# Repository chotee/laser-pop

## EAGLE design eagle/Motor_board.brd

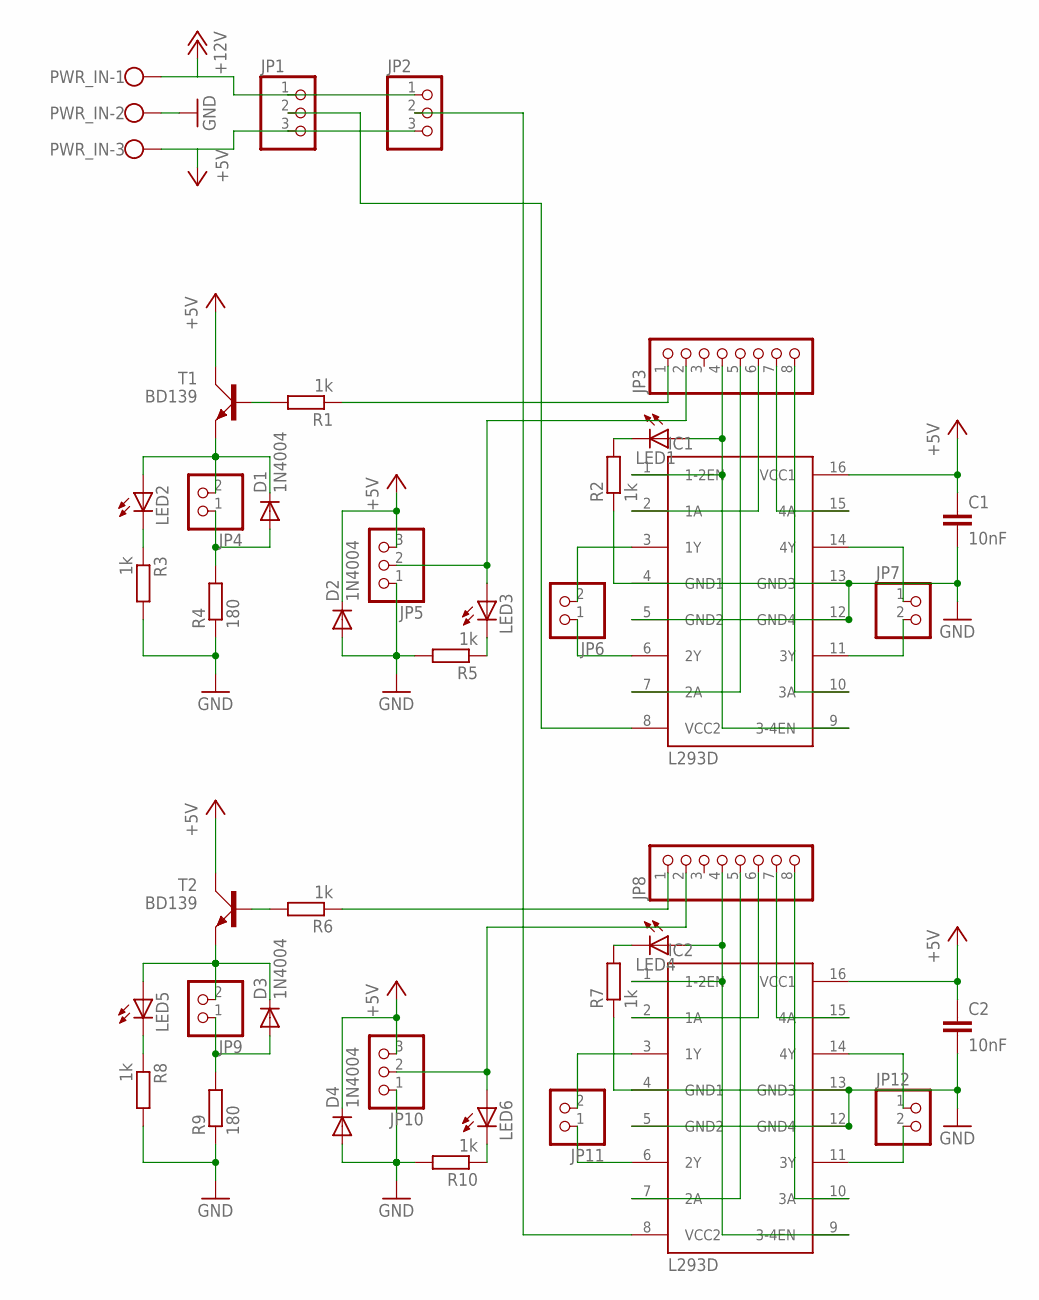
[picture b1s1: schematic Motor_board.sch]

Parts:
C1, C2: 10nF; C050-024X044
D1, D2, D3, D4: 1N4004; DO41-10
IC1, IC2: L293D; DIL16
JP1, JP2, JP5, JP10: PINHD-1X3; 1X03
JP3, JP8: PINHD-1X8; 1X08
JP4, JP6, JP7, JP9, JP11, JP12: PINHD-1X2; 1X02
LED1, LED2, LED3, LED4, LED5, LED6: LED3MM
PWR_IN: W237-103
R1, R2, R3, R5, R6, R7, R8, R10: 1k; 0207/7
R4, R9: 180; 0414V
T1, T2: BD139; TO126AV

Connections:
+5V: C1.1, C2.1, D2.C, D4.C, IC1.16 (VCC1), IC2.16 (VCC1), JP1.3, JP2.3, JP5.3, JP10.3, PWR_IN.3, T1.C, T2.C
+12V: JP1.1, JP2.1, PWR_IN.1
GND: C1.2, C2.2, D2.A, D4.A, IC1.4 (GND1), IC1.5 (GND2), IC1.12 (GND4), IC1.13 (GND3), IC2.4 (GND1), IC2.5 (GND2), IC2.12 (GND4), IC2.13 (GND3), JP5.1, JP10.1, PWR_IN.2, R2.1, R3.2, R4.1, R5.2, R7.1, R8.2, R9.1, R10.2
MTR_PWR1: IC1.8 (VCC2), JP1.2
MTR_PWR2: IC2.8 (VCC2), JP2.2
unnamed: IC2.1 (1-2EN), IC2.9 (3-4EN), JP8.4, LED4.A
unnamed: IC2.2 (1A), JP8.6
unnamed: IC2.7 (2A), JP8.5
unnamed: IC2.3 (1Y), JP11.2
unnamed: IC2.6 (2Y), JP11.1
unnamed: IC2.11 (3Y), JP12.2
unnamed: IC1.1 (1-2EN), IC1.9 (3-4EN), JP3.4, LED1.A
unnamed: IC1.10 (3A), JP3.8
unnamed: IC2.14 (4Y), JP12.1
unnamed: IC1.2 (1A), JP3.6
unnamed: IC1.7 (2A), JP3.5
unnamed: IC1.15 (4A), JP3.7
unnamed: IC2.10 (3A), JP8.8
unnamed: IC1.3 (1Y), JP6.2
unnamed: IC1.6 (2Y), JP6.1
unnamed: IC1.11 (3Y), JP7.2
unnamed: IC1.14 (4Y), JP7.1
unnamed: IC2.15 (4A), JP8.7
unnamed: R6.2, T2.B
unnamed: JP8.1, R6.1
unnamed: JP8.2, JP10.2, LED6.A
unnamed: D3.A, JP9.1, R9.2
unnamed: LED1.K (C), R2.2
unnamed: R1.2, T1.B
unnamed: JP3.1, R1.1
unnamed: D1.A, JP4.1, R4.2
unnamed: JP3.2, JP5.2, LED3.A
unnamed: D3.C, JP9.2, LED5.A, T2.E
unnamed: LED5.K (C), R8.1
unnamed: LED4.K (C), R7.2
unnamed: LED6.K (C), R10.1
unnamed: D1.C, JP4.2, LED2.A, T1.E
unnamed: LED2.K (C), R3.1
unnamed: LED3.K (C), R5.1

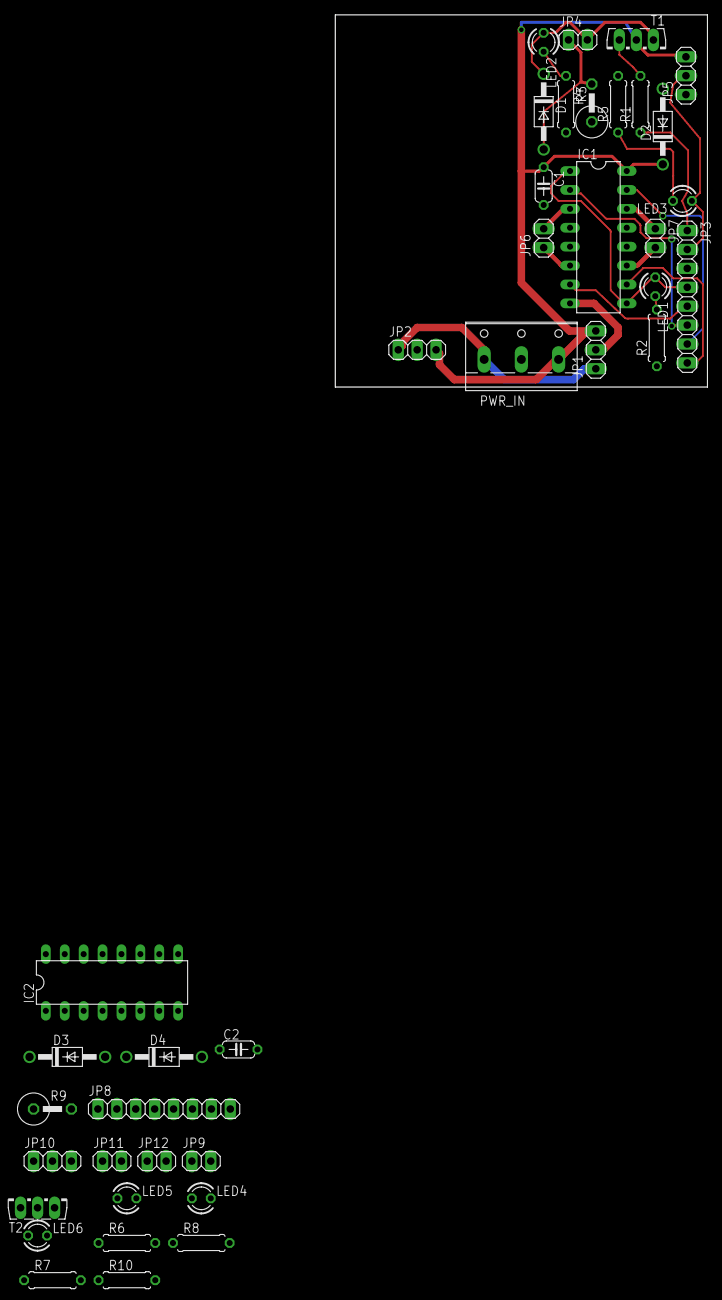
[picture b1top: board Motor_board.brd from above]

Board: 2 copper layers, 50.0 x 50.0 mm, 39 parts (0 on the bottom side), 39 nets.

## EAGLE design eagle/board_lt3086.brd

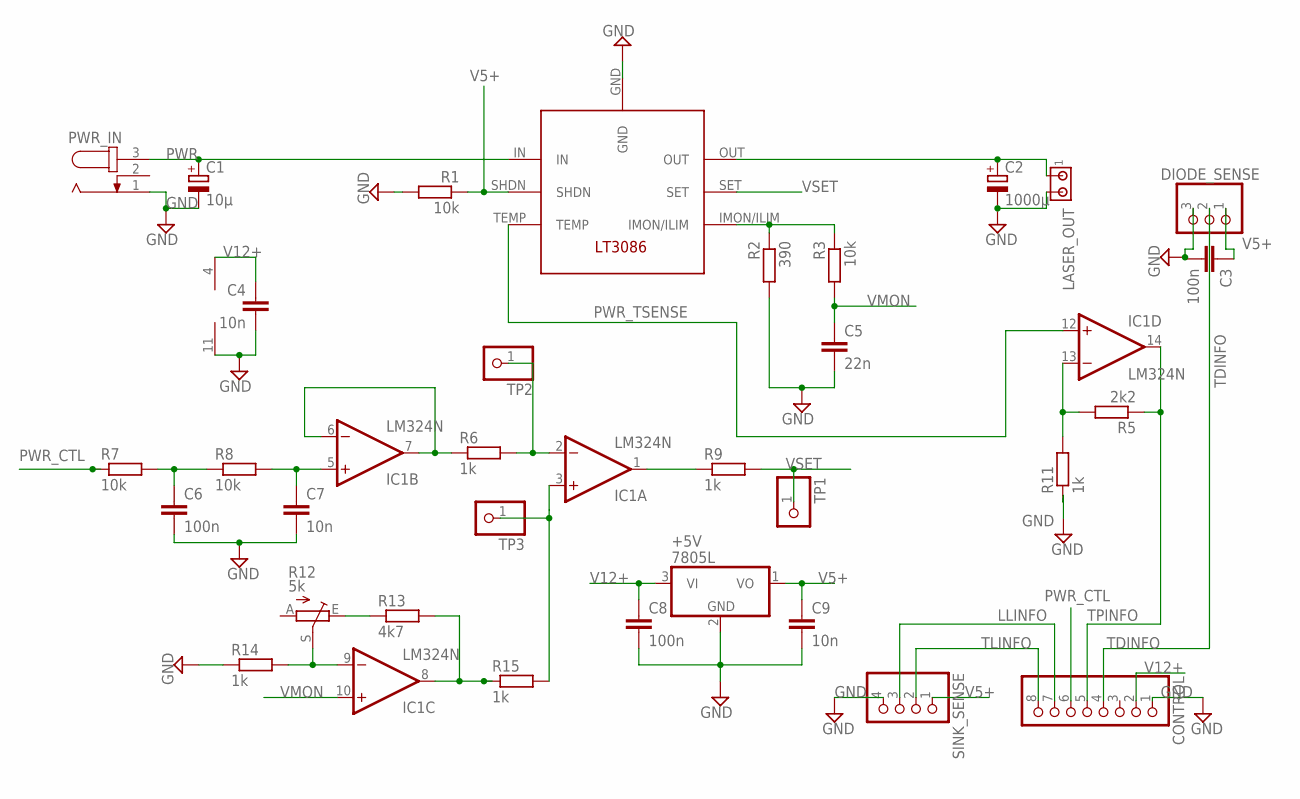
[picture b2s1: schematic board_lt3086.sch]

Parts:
+5V: 7805L; TO92
C1: 10µ; E2,5-7
C2: 1000µ; E3,5-10
C3, C6, C8: 100n; C050-035X075
C4, C7, C9: 10n; C050-024X044
C5: 22n; C050-024X044
CONTROL: PINHD-1X8; 1X08
DIODE_SENSE: PINHD-1X3; 1X03
IC1: LM324N; DIL14
LASER_OUT: 350428-1
PWR_CTRL: LT3086; LT3086-T7
PWR_IN: JACK-PLUG0; SPC4077
R1, R3, R7, R8: 10k; 0207/10
R2: 390; 0207/10
R5: 2k2; 0207/10
R6, R9, R11, R14, R15: 1k; 0207/10
R12: 5k; CA9V
R13: 4k7; 0207/10
SINK_SENSE: PINHD-1X4; 1X04
TP1, TP2, TP3: PINHD-1X1; 1X01

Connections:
GND: +5V.2 (GND), C1.-, C2.-, C3.2, C4.2, C5.2, C6.2, C7.2, C8.2, C9.2, CONTROL.1, DIODE_SENSE.3, IC1.11 (V-), LASER_OUT.2, PWR_CTRL.GND, PWR_IN.1, R1.2, R2.2, R11.1, R14.1, SINK_SENSE.4
LLINFO: CONTROL.7, SINK_SENSE.3
unnamed: IC1.6 (-IN), IC1.7 (OUT), R6.1
unnamed: C7.1, IC1.5 (+IN), R8.2
unnamed: C6.1, R7.2, R8.1
unnamed: IC1.1 (OUT), R9.1
unnamed: IC1.13 (-IN), R5.2, R11.2
unnamed: IC1.2 (-IN), R6.2, TP2.1
unnamed: IC1.3 (+IN), R15.2, TP3.1
unnamed: IC1.8 (OUT), R13.2, R15.1
unnamed: R12.E, R13.1
unnamed: IC1.9 (-IN), R12.S, R14.2
unnamed: PWR_CTRL.IMON/ILIM, R2.1, R3.1
PWR: C1.+, PWR_CTRL.IN, PWR_IN.3
PWR_CTL: CONTROL.6, R7.1
PWR_TSENSE: IC1.12 (+IN), PWR_CTRL.TEMP
TDINFO: CONTROL.4, DIODE_SENSE.2
TLINFO: CONTROL.8, SINK_SENSE.2
TPINFO: CONTROL.5, IC1.14 (OUT), R5.1
V5+: +5V.1 (VO), C3.1, C9.1, DIODE_SENSE.1, PWR_CTRL.SHDN, R1.1, SINK_SENSE.1
V12+: +5V.3 (VI), C4.1, C8.1, CONTROL.2, IC1.4 (V+)
VMON: C5.1, IC1.10 (+IN), R3.2
VOUT: C2.+, LASER_OUT.1, PWR_CTRL.OUT
VSET: PWR_CTRL.SET, R9.2, TP1.1

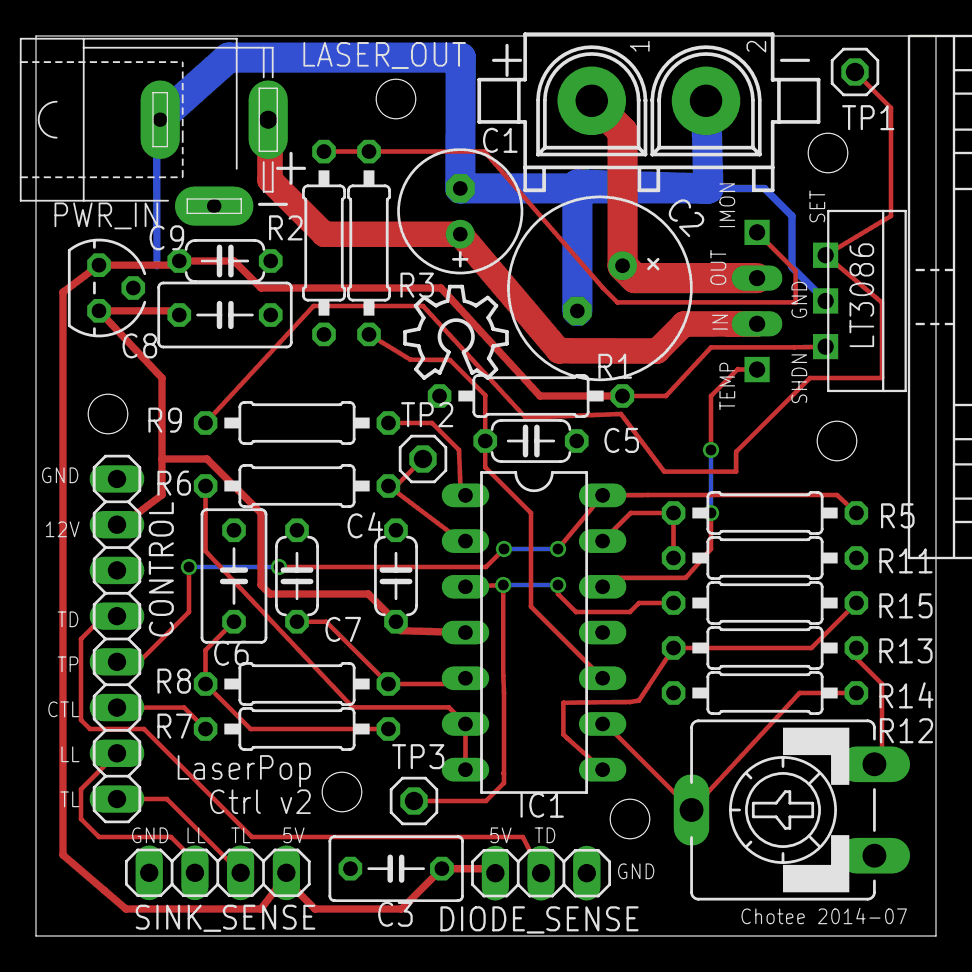
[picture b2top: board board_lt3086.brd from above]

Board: 2 copper layers, 50.0 x 50.0 mm, 35 parts (0 on the bottom side), 24 nets.

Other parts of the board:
U$1: OSHW_8X200_NOTEXT
U$2: HEATSINK-11C/W

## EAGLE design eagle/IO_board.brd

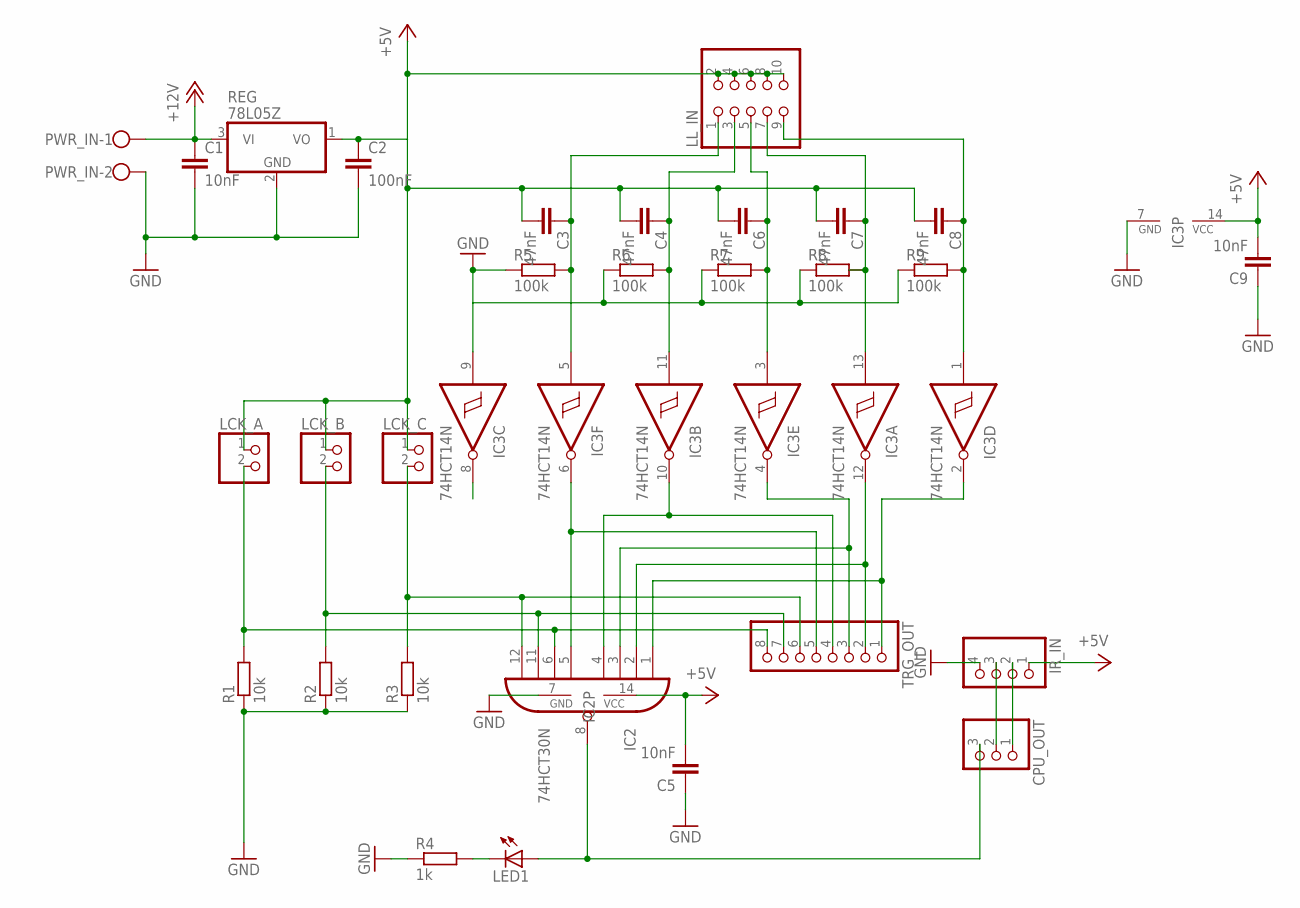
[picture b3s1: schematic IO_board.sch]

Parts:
C1: 10nF; C025-025X050
C2: 100nF; C025-025X050
C3, C4, C6, C7, C8: 47nF; C025-025X050
C5, C9: 10nF; C050-024X044
CPU_OUT: PINHD-1X3; 1X03
IC2: 74HCT30N; DIL14
IC3: 74HCT14N; DIL14
IR_IN: PINHD-1X4; 1X04
LCK_A: PINHD-1X2; 1X02
LCK_B: PINHD-1X2; 1X02
LCK_C: PINHD-1X2; 1X02
LED1: LED3MM
LL_IN: PINHD-2X5; 2X05
PWR_IN: W237-102
R1, R2, R3: 10k; 0207/7
R4: 1k; 0207/7
R5, R6, R7, R8, R9: 100k; 0207/7
REG: 78L05Z; TO92
TRG_OUT: PINHD-1X8; 1X08

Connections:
+5V: C2.1, C3.2, C4.2, C5.2, C6.2, C7.2, C8.2, C9.2, IC2.14 (VCC), IC3.14 (VCC), IR_IN.1, LCK_A.1, LCK_B.1, LCK_C.1, LL_IN.2, LL_IN.4, LL_IN.6, LL_IN.8, LL_IN.10, REG.1 (VO)
+12V: C1.1, PWR_IN.1, REG.3 (VI)
GND: C1.2, C2.2, C5.1, C9.1, IC2.7 (GND), IC3.7 (GND), IR_IN.4, PWR_IN.2, R1.1, R2.1, R3.1, R4.1, R5.1, R6.1, R7.1, R8.1, R9.1, REG.2 (GND)
unnamed: IC2.2 (I1), IC3.12 (O), TRG_OUT.2
unnamed: IC2.4 (I3), IC3.10 (O), TRG_OUT.4
unnamed: IC2.1 (I0), IC3.2 (O), TRG_OUT.1
unnamed: CPU_OUT.3, IC2.8 (O), LED1.A
unnamed: C4.1, IC3.11 (I), LL_IN.3, R6.2
unnamed: CPU_OUT.2, IR_IN.3
unnamed: C6.1, IC3.3 (I), LL_IN.5, R7.2
unnamed: C7.1, IC3.13 (I), LL_IN.7, R8.2
unnamed: C8.1, IC3.1 (I), LL_IN.9, R9.2
unnamed: CPU_OUT.1, IR_IN.2
unnamed: IC2.5 (I4), IC3.6 (O), TRG_OUT.5
unnamed: C3.1, IC3.5 (I), LL_IN.1, R5.2
unnamed: IC2.3 (I2), IC3.4 (O), TRG_OUT.3
unnamed: IC2.12 (I7), LCK_C.2, R3.2, TRG_OUT.6
unnamed: IC2.11 (I6), LCK_B.2, R2.2, TRG_OUT.7
unnamed: IC2.6 (I5), LCK_A.2, R1.2, TRG_OUT.8
unnamed: LED1.K (C), R4.2

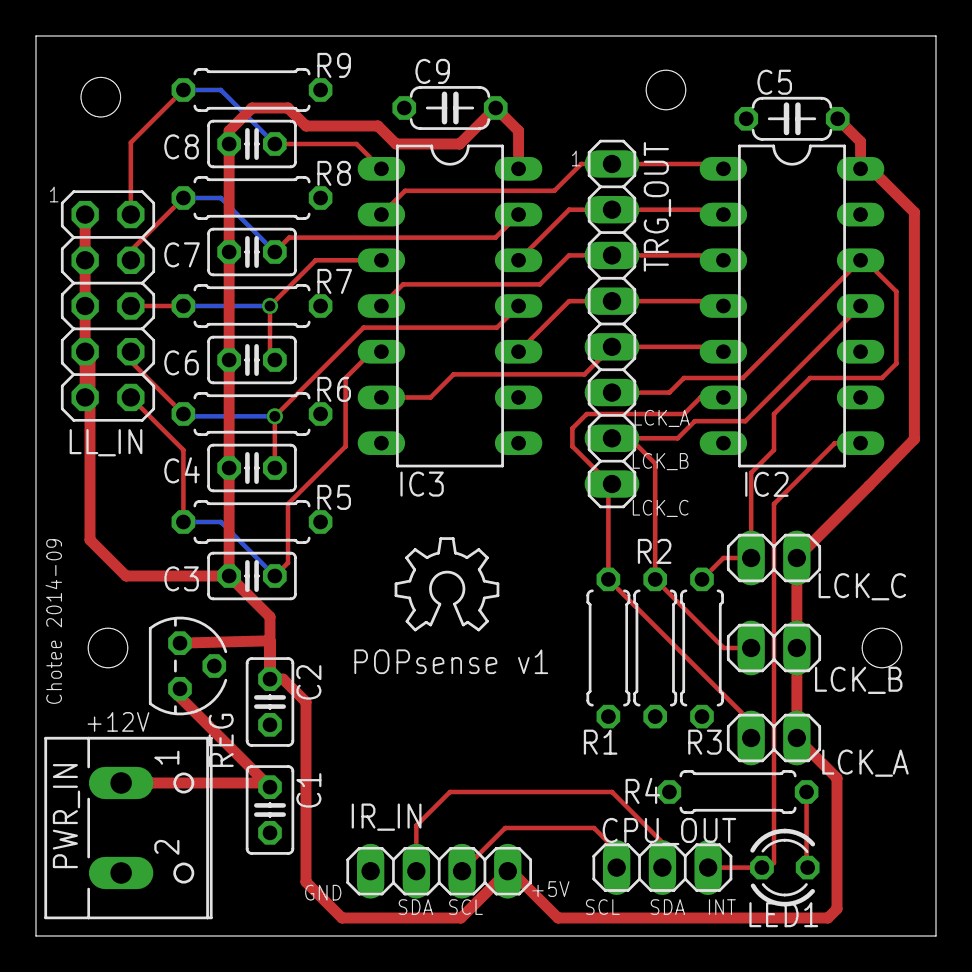
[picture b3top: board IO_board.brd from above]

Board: 2 copper layers, 50.0 x 50.0 mm, 31 parts (0 on the bottom side), 20 nets.

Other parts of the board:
U$1: OSHW_6X200_NOTEXT

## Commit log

2014-09-24 Initial Checkin
2014-09-24 Incorporating PID control for temperature regulation. Source: http://playground.arduino.cc/Code/PIDLibrary
2015-07-23 Restarting dome design effort. Added design for laser mount and lens.
2015-07-23 Dome is now existing.
2015-07-24 Initial multi-laser staggered setup.
2015-07-26 changed colours.
2015-07-26 Added the bottom anti-dome.
2015-07-26 Fixed typo.
2015-07-26 added laser beam.
2015-07-26 State: Experimenting with handling of dome connections
2015-07-28 State: experimenting with proper definition of connectors.
